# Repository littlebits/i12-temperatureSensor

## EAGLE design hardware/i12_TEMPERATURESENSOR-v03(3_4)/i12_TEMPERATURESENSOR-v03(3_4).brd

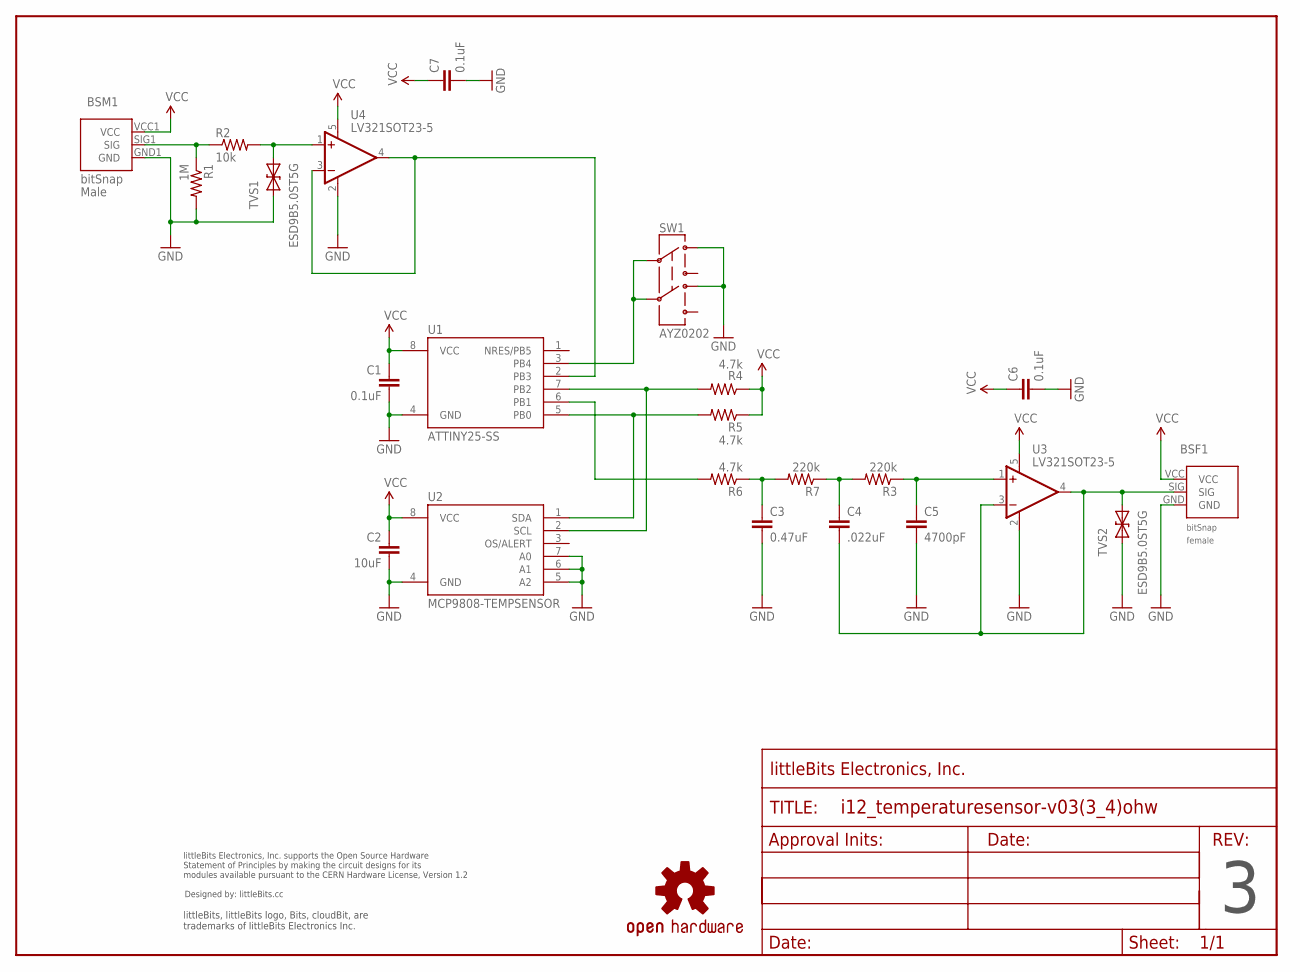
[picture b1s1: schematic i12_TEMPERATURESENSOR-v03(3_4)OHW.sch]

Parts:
BSF1: BITSNAP_V03_FEMALE
BSM1: BITSNAP_V03_MALE
C1, C6, C7: 0.1uF; CAP-0603
C2: 10uF; CAP-0603
C3: 0.47uF; CAP-0603
C4: .022uF; CAP-0603
C5: 4700pF; CAP-0603
R1: 1M; RES-0603
R2: 10k; RES-0603
R3, R7: 220k; RES-0603
R4, R5, R6: 4.7k; RES-0603
SW1: AYZ0202
TVS1, TVS2: ESD9B5.0ST5G; SOD-923
U1: ATTINY25-SS; SOIC08_JEDEC_150MIL
U2: MCP9808-TEMPSENSOR; MICRO8-ON
U3, U4: LV321SOT23-5; SOT23-5
U$4: OSHWCREDIT
U$5: OSHW-LOGOL; OSHW-LOGO-L
U$33: FRAME-LETTER-OHWOHW; FABDWG01-OHW

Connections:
GND: BSF1.GND, BSM1.GND1 (GND), C1.2, C2.2, C3.2, C5.2, C6.2, C7.2, R1.2, SW1.1, SW1.4, TVS1.1 (A), TVS2.1 (A), U1.4 (GND), U2.4 (GND), U2.5 (A2), U2.6 (A1), U2.7 (A0), U3.2 (V-), U4.2 (V-)
unnamed: R6.2, U1.6 (PB1)
unnamed: SW1.2, SW1.5, U1.3 (PB4)
unnamed: C3.1, R6.1, R7.2
unnamed: R2.2, TVS1.2 (C), U4.1 (+IN)
unnamed: BSM1.SIG1 (SIG), R1.1, R2.1
unnamed: C4.1, R3.2, R7.1
unnamed: C5.1, R3.1, U3.1 (+IN)
unnamed: R5.2, U1.5 (PB0), U2.1 (SDA)
unnamed: R4.2, U1.7 (PB2), U2.2 (SCL)
unnamed: BSF1.SIG, C4.2, TVS2.2 (C), U3.3 (-IN), U3.4 (OUT)
SIG: U1.2 (PB3), U4.3 (-IN), U4.4 (OUT)
VCC: BSF1.VCC, BSM1.VCC1 (VCC), C1.1, C2.1, C6.1, C7.1, R4.1, R5.1, U1.8 (VCC), U2.8 (VCC), U3.5 (V+), U4.5 (V+)

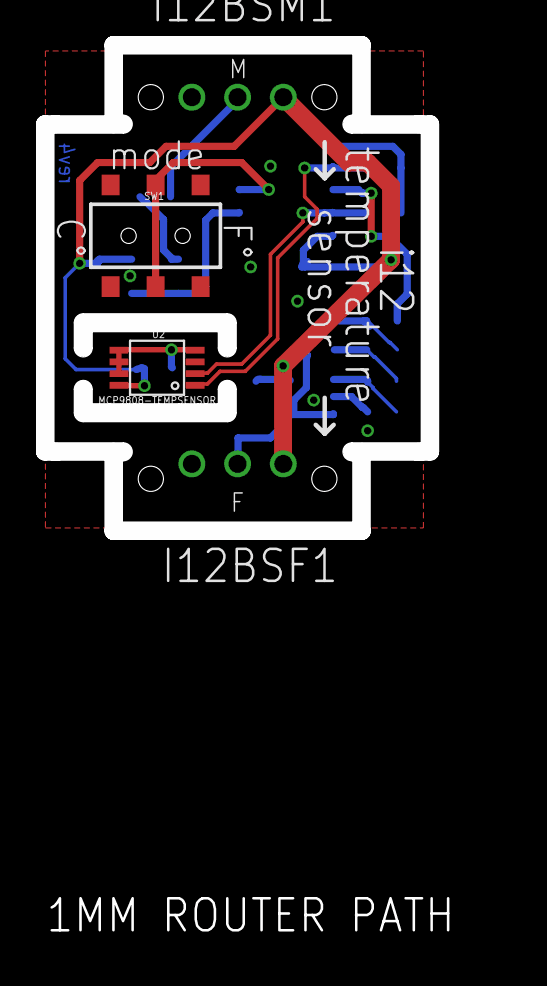
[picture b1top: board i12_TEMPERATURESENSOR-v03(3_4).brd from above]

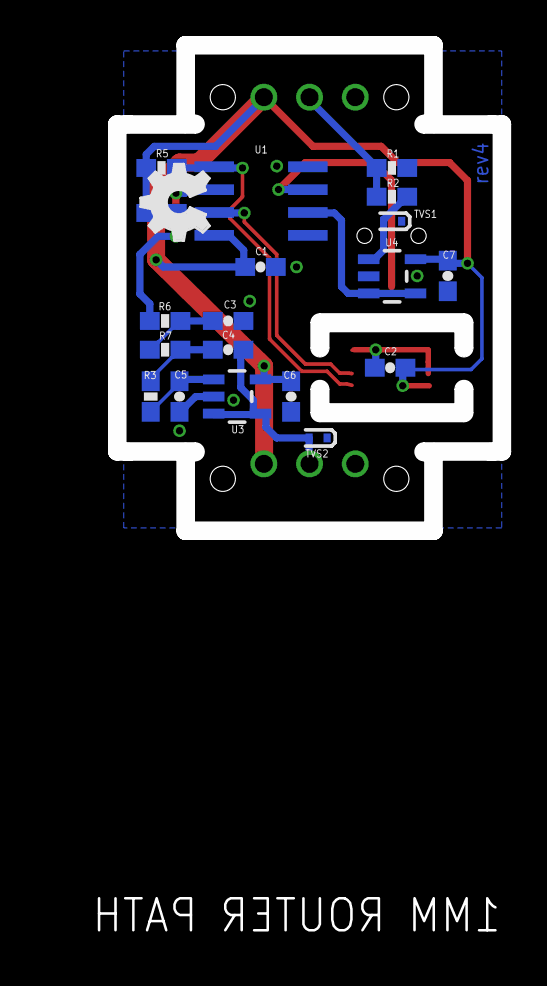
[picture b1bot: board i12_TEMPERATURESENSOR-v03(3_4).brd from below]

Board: 2 copper layers, 25.4 x 49.8 mm, 28 parts (20 on the bottom side), 13 nets.

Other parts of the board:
DRILEGEND: DRILEGEND
U$32: OSHW_FILLX150_NOTEXT

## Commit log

2014-11-18 First commit, added hardware and firmware
2014-11-18 Added README, changed hardware file structure

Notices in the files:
parts and their libraries:
LITTLEBITS: modules available pursuant to the CERN Hardware License,
Version 1.2
LITTLEBITS: modules available pursuant to the CERN Hardware License, Version 1.2
